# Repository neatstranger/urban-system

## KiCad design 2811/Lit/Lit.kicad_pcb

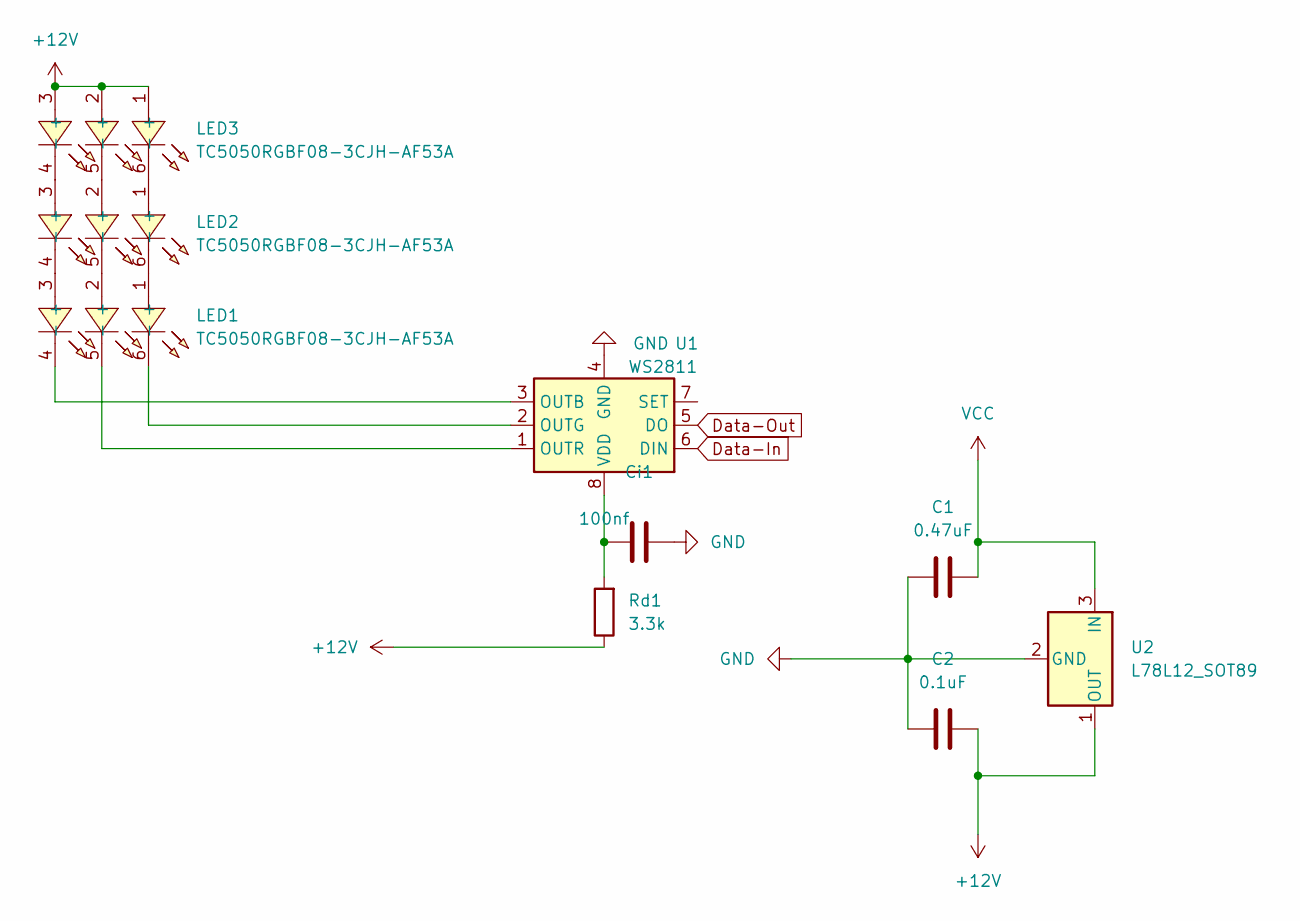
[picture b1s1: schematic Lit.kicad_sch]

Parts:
C1: 0.47uF; C_0201_0603Metric_Pad0.64x0.40mm_HandSolder; LCSC Part C162281
C2: 0.1uF; C_0805_2012Metric; LCSC Part C3011698
Ci1: 100nf; C_0805_2012Metric; LCSC Part C114581
LED1, LED2, LED3: TC5050RGBF08-3CJH-AF53A; LED-SMD_6P-L5.0-W5.0-TL_TC5050RGBF08; LCSC Part C784540
Rd1: 3.3k; R_0201_0603Metric; LCSC Part C108078
U1: WS2811; SOP-8_L4.9-W3.9-P1.27-LS6.0-BL; LCSC Part C114581
U2: L78L12_SOT89; SOT-89-3; LCSC Part C75501

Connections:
+12V: C2.2, LED3.1 (+), LED3.2 (+), LED3.3 (+), Rd1.1, U2.1 (OUT)
Data-In: U1.6 (DIN)
Data-Out: U1.5 (DO)
GND: C1.1, C2.1, Ci1.2, U1.4 (GND), U2.2 (GND)
unnamed: LED1.1 (+), LED2.6 (-)
unnamed: LED1.2 (+), LED2.5 (-)
unnamed: LED1.3 (+), LED2.4 (-)
unnamed: LED2.1 (+), LED3.6 (-)
unnamed: LED2.2 (+), LED3.5 (-)
unnamed: LED2.3 (+), LED3.4 (-)
unnamed: LED1.4 (-), U1.3 (OUTB)
unnamed: LED1.6 (-), U1.2 (OUTG)
unnamed: LED1.5 (-), U1.1 (OUTR)
unnamed: Ci1.1, Rd1.2, U1.8 (VDD)
VCC: C1.2, U2.3 (IN)

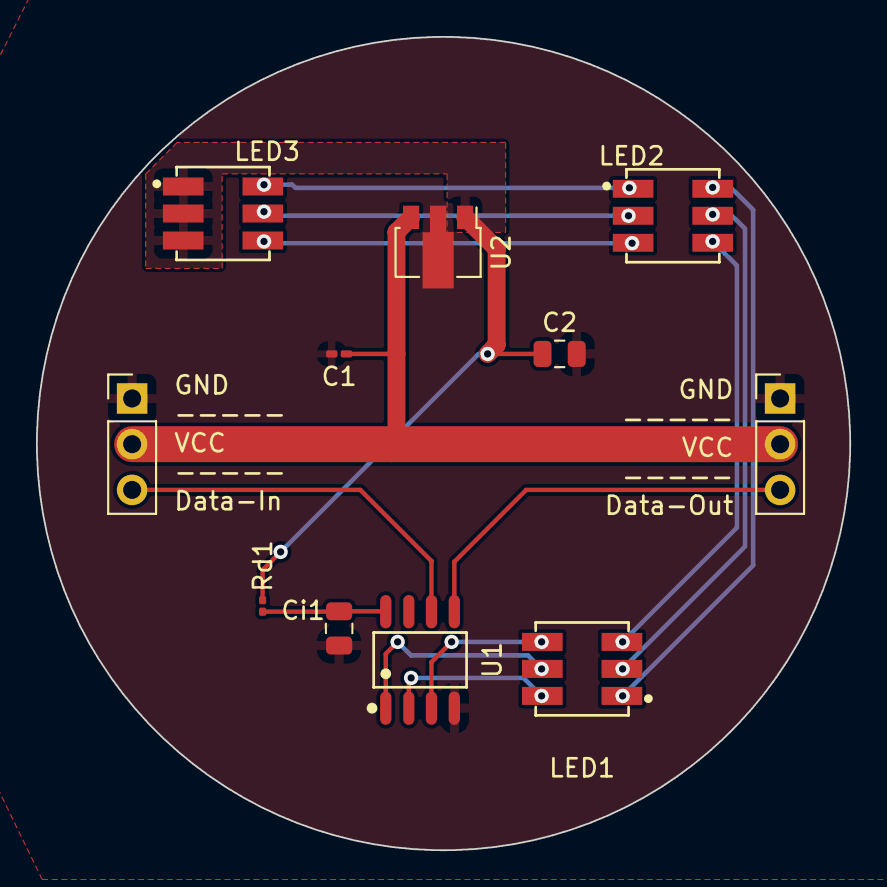
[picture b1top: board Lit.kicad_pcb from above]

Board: 2 copper layers, 45.2 x 45.2 mm, 9 parts (0 on the bottom side), 13 nets.

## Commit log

2023-12-08 Push WS2811
2023-12-08 Working
2023-12-08 Added code.
